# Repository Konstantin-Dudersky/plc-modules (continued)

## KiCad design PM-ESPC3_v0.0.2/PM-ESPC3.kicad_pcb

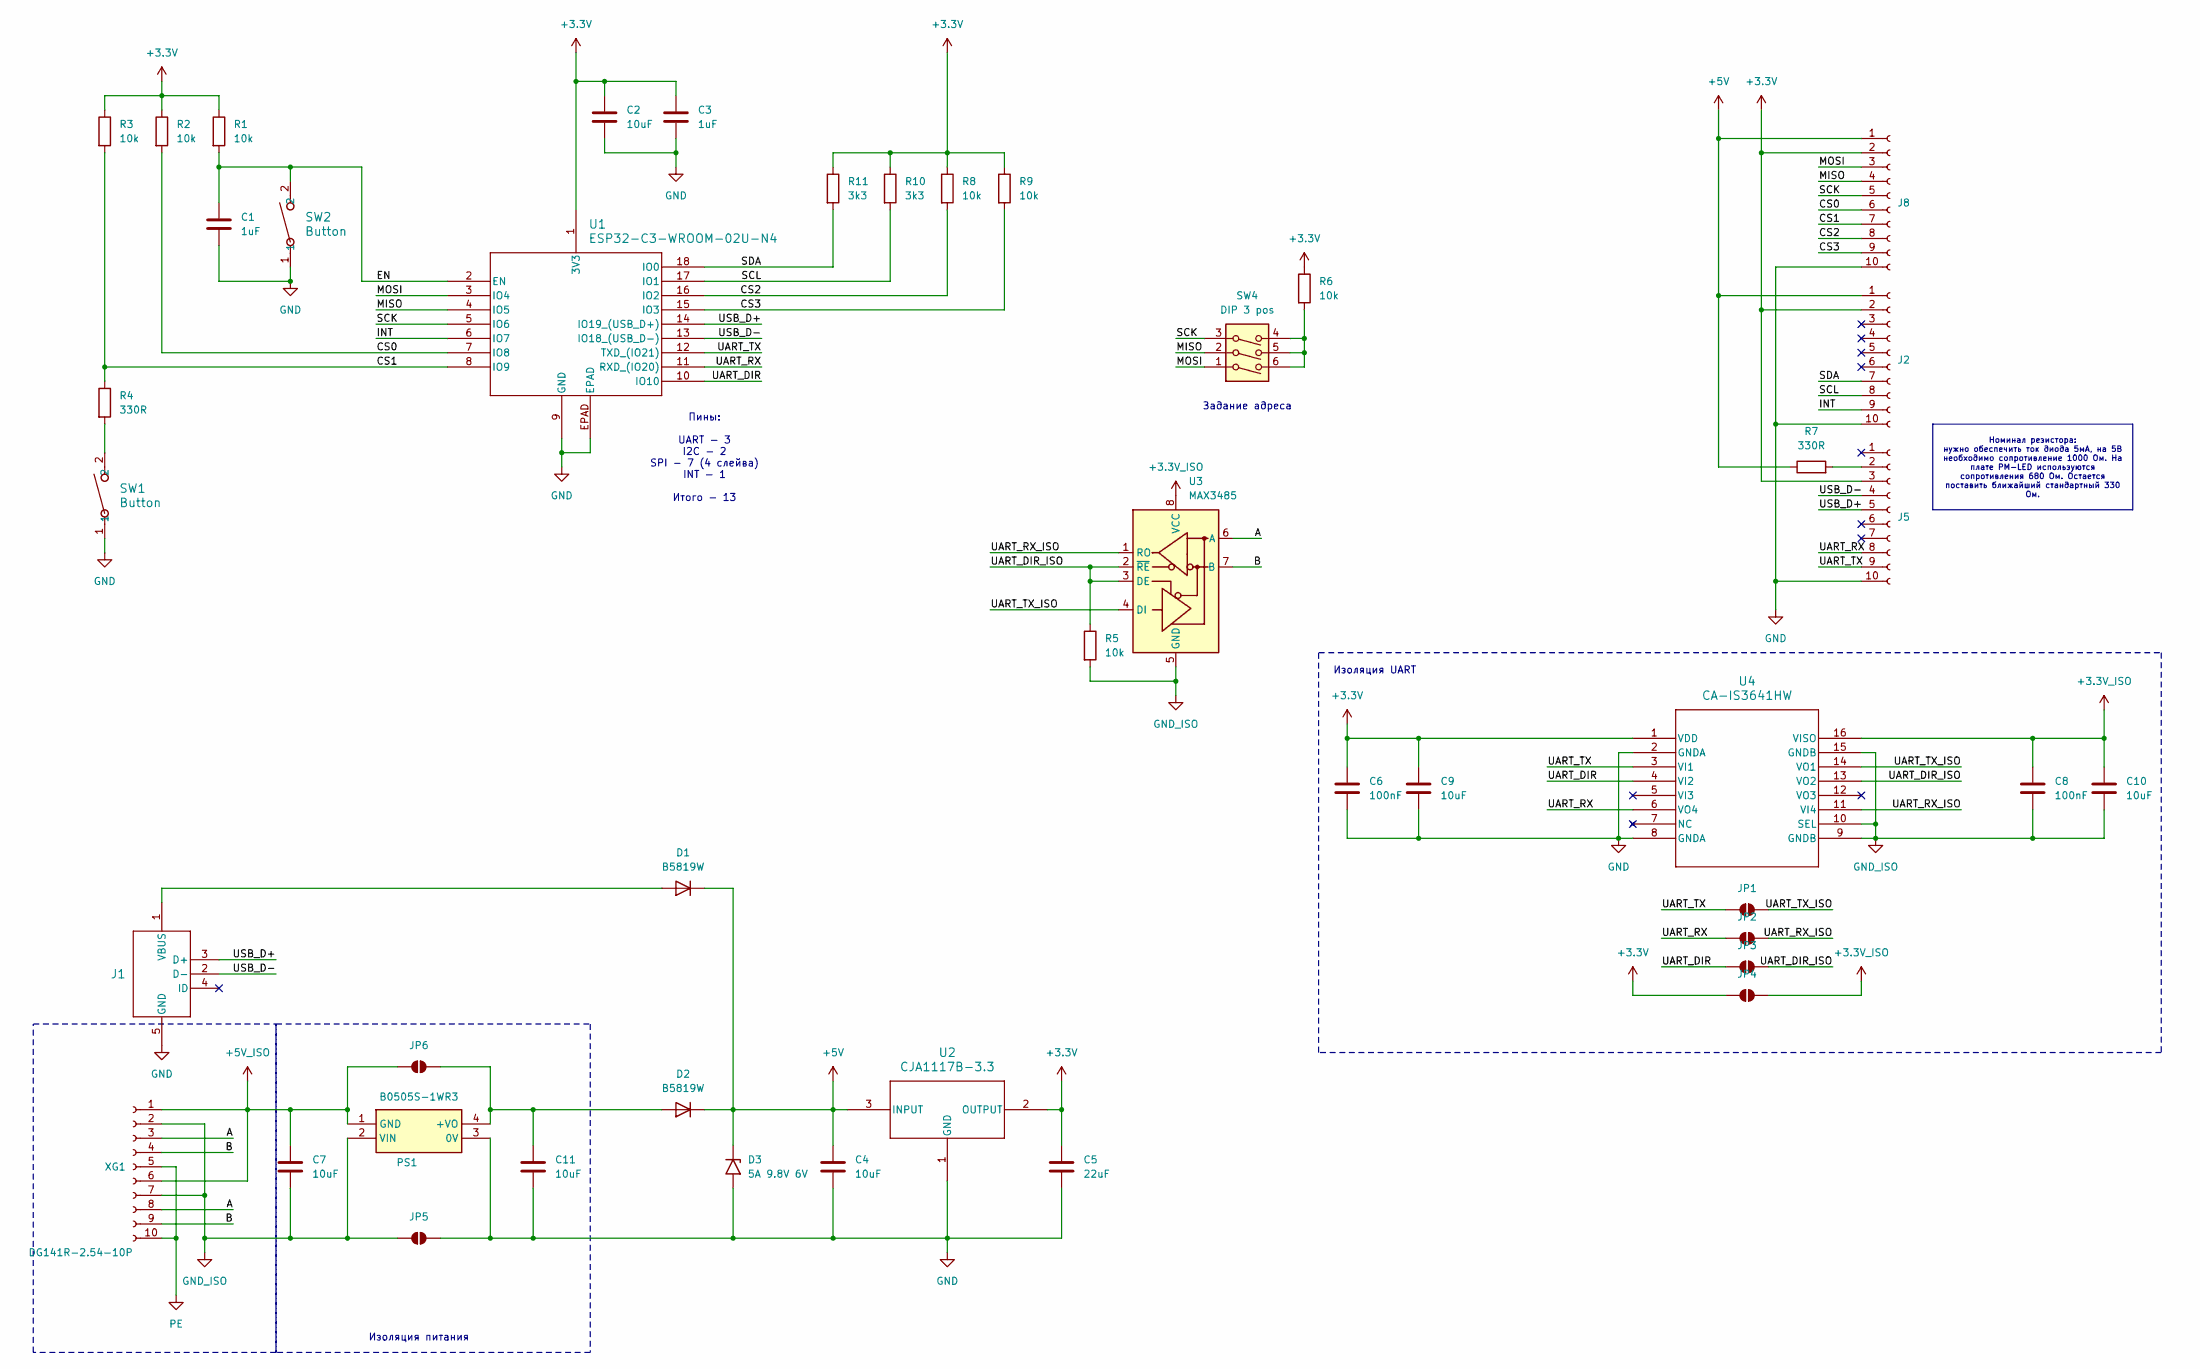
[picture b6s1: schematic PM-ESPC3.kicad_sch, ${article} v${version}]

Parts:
C1, C3: 1uF; C_1206_3216Metric_Pad1.33x1.80mm_HandSolder; part_ipn C_1uF_16V_1206
C2, C4, C7, C9, C10, C11: 10uF; C_1206_3216Metric_Pad1.33x1.80mm_HandSolder; part_ipn C_10uF_16V_1206
C5: 22uF; C_1206_3216Metric_Pad1.33x1.80mm_HandSolder; part_ipn C_22uF_16V_1206
C6, C8: 100nF; C_1206_3216Metric_Pad1.33x1.80mm_HandSolder; part_ipn C_100nF_50V_1206
D1, D2: B5819W; D_SOD-123; part_ipn B5819W
D3: 5A 9.8V 6V; D_SOD-323_HandSoldering; part_ipn LESD3Z5.0T1G
J1: U254-051T-4BH83-S1S; CONN5_H83-S1S_XKB; part_ipn U254-051T-4BH83-S1S
J2, J5, J8: AFA07-S10FCC-00; CONN10_AFA07-S10_JUS; part_ipn AFA07-S10FCC-00
JP1, JP2, JP3, JP4, JP5, JP6: SolderJumper_2_Open; SolderJumper-2_P1.3mm_Open_RoundedPad1.0x1.5mm
PS1: B0505S-1WR3; B0505S1WR3; Manufacturer_Part_Number B0505S-1WR3
R1, R2, R3, R5, R6, R8, R9: 10k; R_1206_3216Metric_Pad1.30x1.75mm_HandSolder; part_ipn R_10k_1206_1%
R4, R7: 330R; R_1206_3216Metric_Pad1.30x1.75mm_HandSolder; part_ipn R_330R_1206_1%
R10, R11: 3k3; R_1206_3216Metric_Pad1.30x1.75mm_HandSolder; part_ipn R_3k3_1206_1%
SW1, SW2: Button; SW_TS-1088_XNP-M; part_ipn TS-1088-AR02016
SW4: DIP 3 pos; DA03BLP; part_ipn DA-03BLP
U1: ESP32-C3-WROOM-02U-N4; ESP32-C3-WROOM-02U_EXP; part_ipn ESP32-C3-WROOM-02U-N4
U2: CJA1117B-3.3; SOT-89-3; part_ipn CJA1117B-3.3
U3: MAX3485; SOIC-8_3.9x4.9mm_P1.27mm
U4: CA-IS3641HW; SOIC16-WBW_CLG-M; part_ipn CA-IS3641HW
XG1: DG141R-2.54-10P; part_ipn DG141R-2.54-10P

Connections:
+3.3V: C2.2, C3.1, C5.1, C6.1, C9.1, J2.2, J5.3, J8.2, JP4.1 (A), R1.1, R2.1, R3.1, R6.1, R8.1, R9.1, R10.1, R11.1, U1.1 (3V3), U2.2 (OUTPUT), U4.1 (VDD)
+3.3V_ISO: C8.1, C10.1, JP4.2 (B), U3.8 (VCC), U4.16 (VISO)
+5V: C4.1, D1.1 (K), D2.1 (K), D3.1 (A1), J2.1, J8.1, R7.1, U2.3 (INPUT)
+5V_ISO: C7.1, JP6.1 (A), PS1.1 (GND), XG1.1, XG1.6
/A: U3.6 (A), XG1.3, XG1.8
/B: U3.7 (B), XG1.4, XG1.9
/CS0: J8.6, R2.2, U1.7 (IO8)
/CS1: J8.7, R3.2, R4.1, U1.8 (IO9)
/CS2: J8.8, R8.2, U1.16 (IO2)
/CS3: J8.9, R9.2, U1.15 (IO3)
/EN: C1.1, R1.2, SW2.2, U1.2 (EN)
/INT: J2.9, U1.6 (IO7)
/MISO: J8.4, SW4.2, U1.4 (IO5)
/MOSI: J8.3, SW4.1, U1.3 (IO4)
/SCK: J8.5, SW4.3, U1.5 (IO6)
/SCL: J2.8, R10.2, U1.17 (IO1)
/SDA: J2.7, R11.2, U1.18 (IO0)
/UART_DIR: JP3.1 (A), U1.10 (IO10), U4.4 (VI2)
/UART_DIR_ISO: JP3.2 (B), R5.1, U3.2 (~RE), U3.3 (DE), U4.13 (VO2)
/UART_RX: J5.8, JP2.1 (A), U1.11 (RXD_(IO20)), U4.6 (VO4)
/UART_RX_ISO: JP2.2 (B), U3.1 (RO), U4.11 (VI4)
/UART_TX: J5.9, JP1.1 (A), U1.12 (TXD_(IO21)), U4.3 (VI1)
/UART_TX_ISO: JP1.2 (B), U3.4 (DI), U4.14 (VO1)
/USB_D+: J1.3 (D+), J5.5, U1.14 (IO19_(USB_D+))
/USB_D-: J1.2 (D-), J5.4, U1.13 (IO18_(USB_D-))
GND: C1.2, C2.1, C3.2, C4.2, C5.2, C6.2, C9.2, C11.2, D3.2 (A2), J1.5 (GND), J2.10, J5.10, J8.10, JP5.2 (B), PS1.3 (0V), SW1.1, SW2.1, U1.9 (GND), U1.EPAD, U2.1 (GND), U4.2 (GNDA), U4.8 (GNDA)
GND_ISO: C7.2, C8.2, C10.2, JP5.1 (A), PS1.2 (VIN), R5.2, U3.5 (GND), U4.9 (GNDB), U4.10 (SEL), U4.15 (GNDB), XG1.2, XG1.7
unnamed: D1.2 (A), J1.1 (VBUS)
unnamed: C11.1, D2.2 (A), JP6.2 (B), PS1.4 (+VO)
unnamed: J5.2, R7.2
unnamed: R4.2, SW1.2
unnamed: R6.2, SW4.4, SW4.5, SW4.6
PE: XG1.5, XG1.10

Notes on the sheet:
Номинал резистора: нужно обеспечить ток диода 5мА, на 5В необходимо сопротивление 1000 Ом. На плате PM-LED используются сопротивления 680 Ом. Остается поставить ближайший стандартный 330 Ом.
Задание адреса
Пины: UART - 3 I2C - 2 SPI - 7 (4 слейва) INT - 1 Итого - 13
Изоляция UART
Изоляция питания

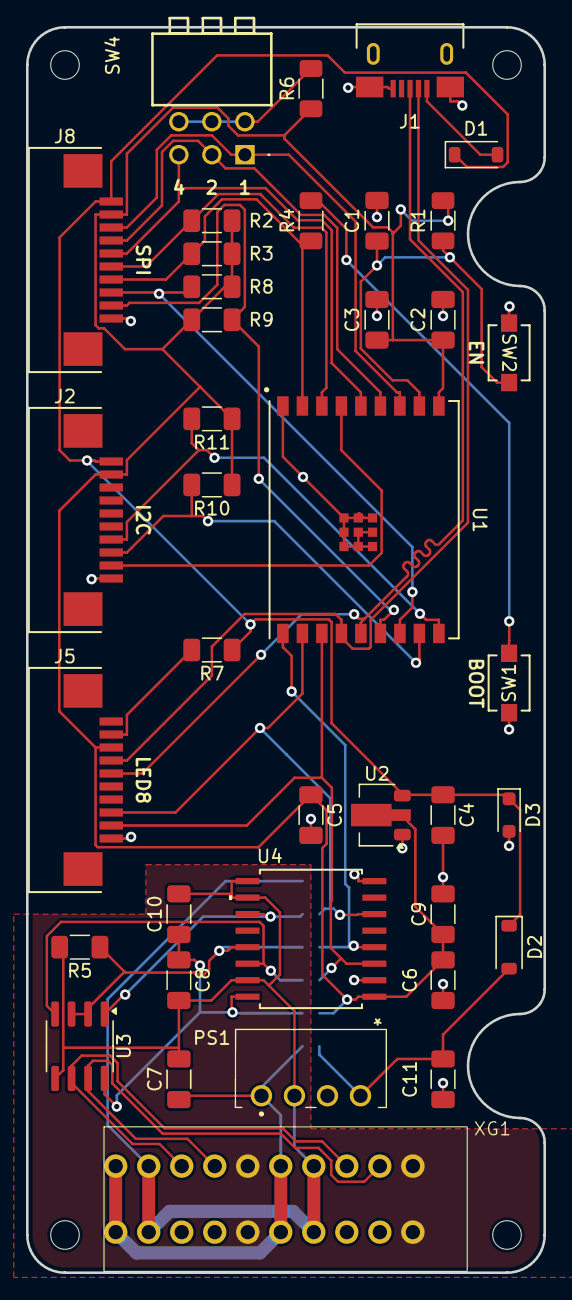
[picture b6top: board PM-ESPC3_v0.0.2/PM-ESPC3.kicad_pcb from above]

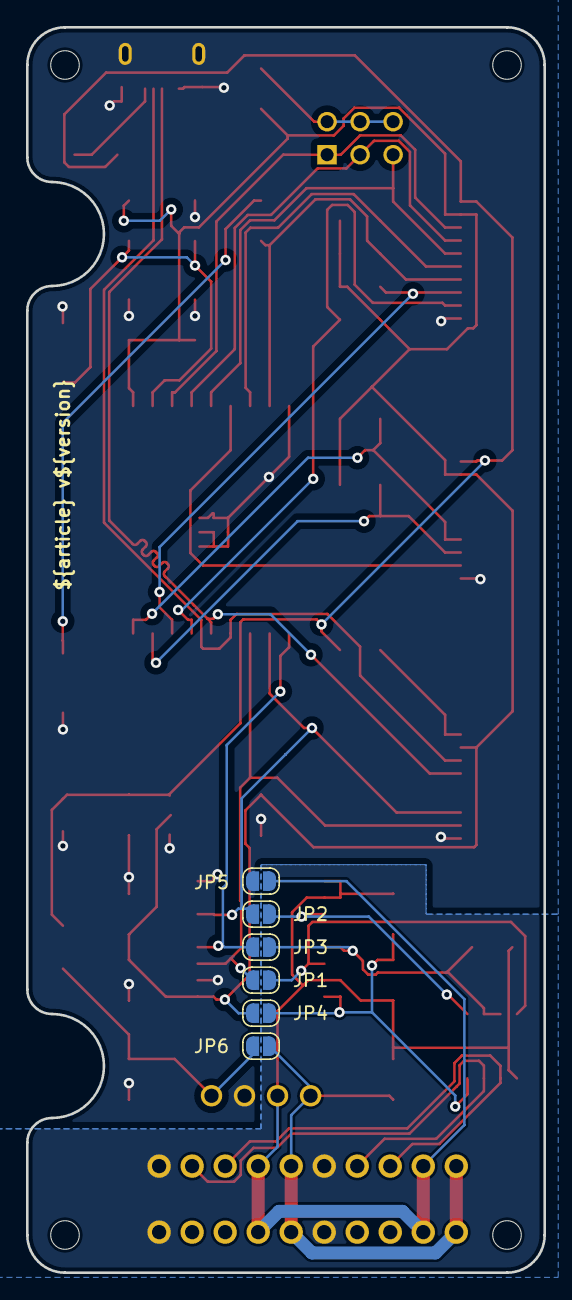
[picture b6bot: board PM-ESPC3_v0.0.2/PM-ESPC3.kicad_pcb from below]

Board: 2 copper layers, 39.8 x 95.8 mm, 44 parts (6 on the bottom side), 33 nets.
